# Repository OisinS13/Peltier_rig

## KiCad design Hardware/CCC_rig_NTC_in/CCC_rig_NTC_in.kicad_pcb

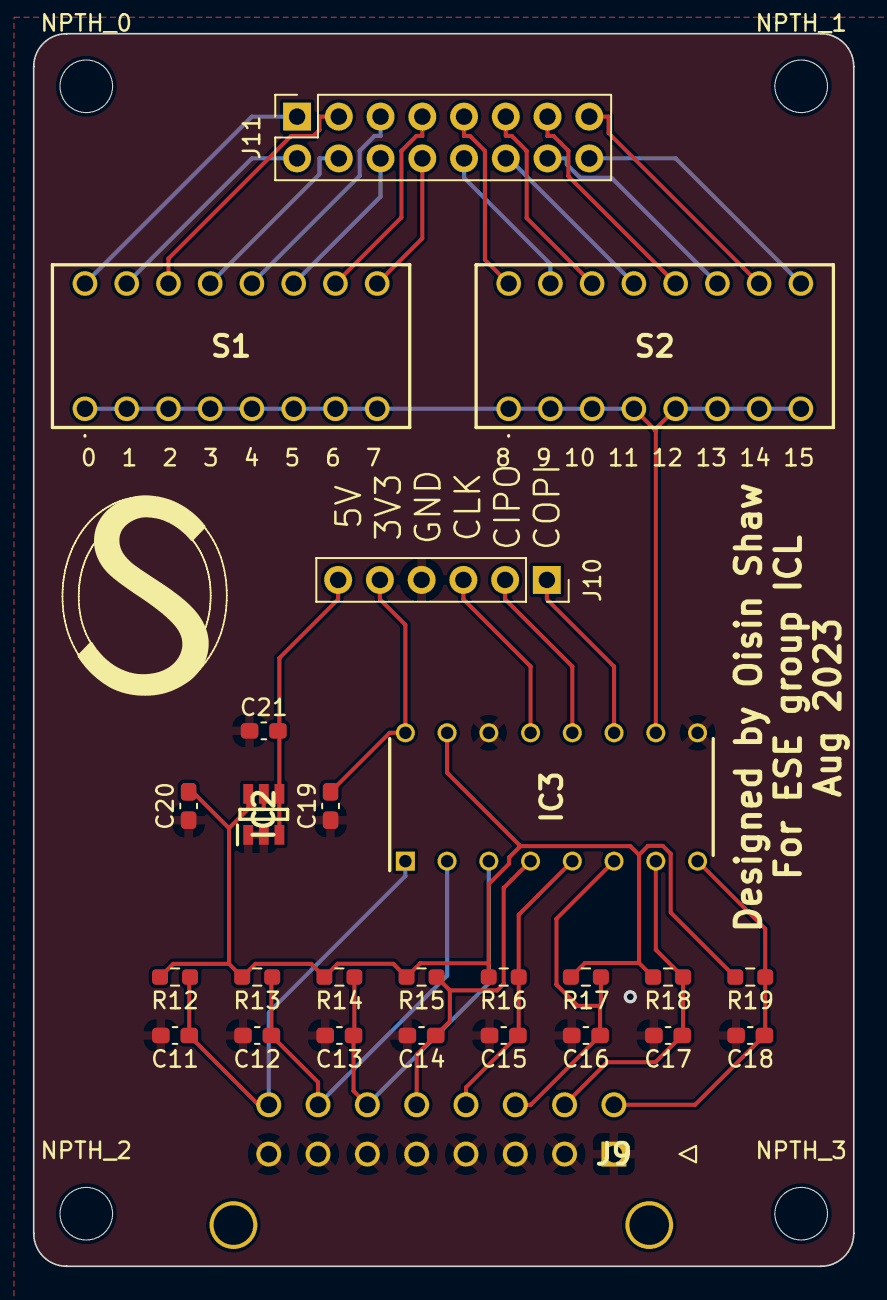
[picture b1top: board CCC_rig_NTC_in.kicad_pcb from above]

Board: 2 copper layers, 49.9 x 75.0 mm, 30 parts (0 on the bottom side), 32 nets.

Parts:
C11, C12, C13, C14, C15, C16, C17, C18, C19, C20: 10 nF; C_0603_1608Metric_Pad1.08x0.95mm_HandSolder
C21: 1 uF; C_0603_1608Metric_Pad1.08x0.95mm_HandSolder
IC2: REF3433IDBVR; SOT95P280X145-6N
IC3: MCP3304-CI_P; DIP781W56P254L1918H533Q16N
J9: NTC_Conn; 43045-16YY_212223
J10: NTC_ADC_Conn; PinSocket_1x06_P2.54mm_Vertical
J11: NTC_ADC_CS_Conn; PinSocket_2x08_P2.54mm_Vertical
NPTH_0, NPTH_1, NPTH_2, NPTH_3: MountingHole_3.2mm_M3_ISO7380
R12, R13, R14, R15, R16, R17, R18, R19: 6.8k; R_0603_1608Metric_Pad0.98x0.95mm_HandSolder
S1, S2: DS01C-254-S-08BE; DS01C254S08BE

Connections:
3V3_ref_NTC_ADC: C20.2, IC2.5 (OUT_S), IC2.6 (OUT_F), IC3.15 (VREF), R12.2, R13.2, R14.2, R15.2, R16.2, R17.2, R18.2, R19.2
+3.3V: C19.2, IC3.16 (VDD), J10.5
+5V: C21.2, IC2.3 (ENABLE), IC2.4 (IN), J10.6
ADC_SPI_CLK: IC3.13 (CLK), J10.3
ADC_SPI_MISO: IC3.12 (DOUT), J10.2
ADC_SPI_MOSI: IC3.11 (DIN), J10.1
GNDD: C11.2, C12.2, C13.2, C14.2, C15.2, C16.2, C17.2, C18.2, C19.1, C20.1, C21.1, IC2.1 (GND_F), IC2.2 (GND_S), IC3.9 (DGND), IC3.14 (AGND), J9.1, J9.2, J9.3, J9.4, J9.5, J9.6, J9.7, J9.8, J10.4
NTC_ADC_CH0: C11.1, IC3.1 (CH0), J9.16, R12.1
NTC_ADC_CH1: C12.1, IC3.2 (CH1), J9.15, R13.1
NTC_ADC_CH2: C13.1, IC3.3 (CH2), J9.14, R14.1
NTC_ADC_CH3: C14.1, IC3.4 (CH3), J9.13, R15.1
NTC_ADC_CH4: C15.1, IC3.5 (CH4), J9.12, R16.1
NTC_ADC_CH5: C16.1, IC3.6 (CH5), J9.11, R17.1
NTC_ADC_CH6: C17.1, IC3.7 (CH6), J9.10, R18.1
NTC_ADC_CH7: C18.1, IC3.8 (CH7), J9.9, R19.1
NTC_ADC_CS: IC3.10 (~CS/SHDN), S1.1 (COM_1), S1.3 (COM_2), S1.5 (COM_3), S1.7 (COM_4), S1.9 (COM_5), S1.11 (COM_6), S1.13 (COM_7), S1.15 (COM_8), S2.1 (COM_1), S2.3 (COM_2), S2.5 (COM_3), S2.7 (COM_4), S2.9 (COM_5), S2.11 (COM_6), S2.13 (COM_7), S2.15 (COM_8)
NTC_ADC_CS_00: J11.1, S1.2 (NO_1)
NTC_ADC_CS_01: J11.2, S1.4 (NO_2)
NTC_ADC_CS_02: J11.3, S1.6 (NO_3)
NTC_ADC_CS_03: J11.4, S1.8 (NO_4)
NTC_ADC_CS_04: J11.5, S1.10 (NO_5)
NTC_ADC_CS_05: J11.6, S1.12 (NO_6)
NTC_ADC_CS_06: J11.7, S1.14 (NO_7)
NTC_ADC_CS_07: J11.8, S1.16 (NO_8)
NTC_ADC_CS_08: J11.9, S2.2 (NO_1)
NTC_ADC_CS_09: J11.10, S2.4 (NO_2)
NTC_ADC_CS_10: J11.11, S2.6 (NO_3)
NTC_ADC_CS_11: J11.12, S2.8 (NO_4)
NTC_ADC_CS_12: J11.13, S2.10 (NO_5)
NTC_ADC_CS_13: J11.14, S2.12 (NO_6)
NTC_ADC_CS_14: J11.15, S2.14 (NO_7)
NTC_ADC_CS_15: J11.16, S2.16 (NO_8)

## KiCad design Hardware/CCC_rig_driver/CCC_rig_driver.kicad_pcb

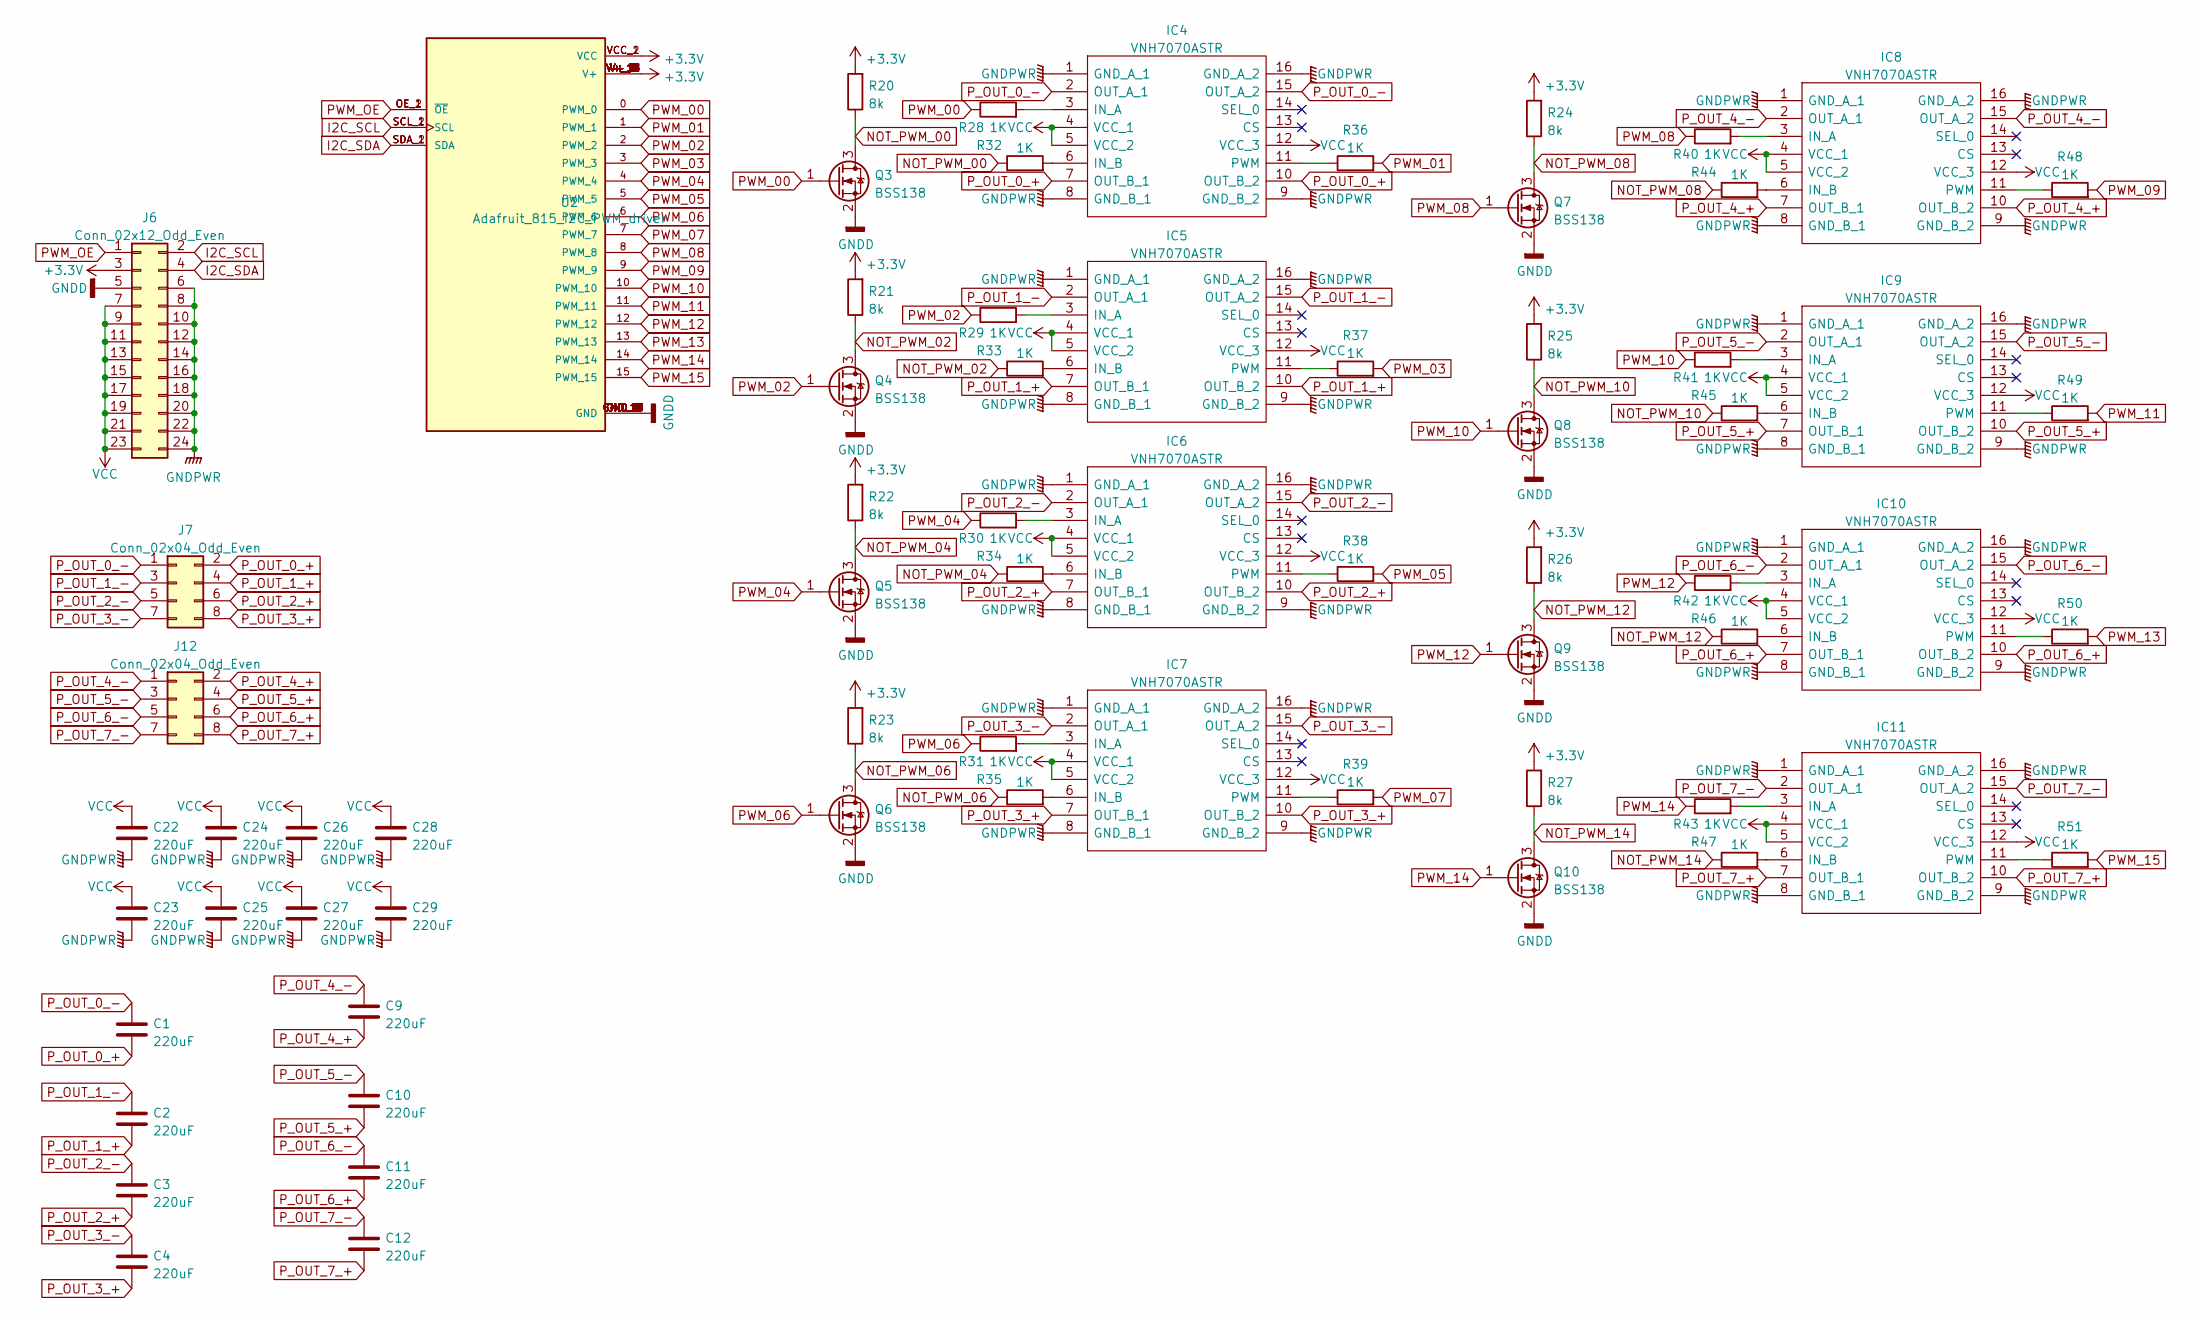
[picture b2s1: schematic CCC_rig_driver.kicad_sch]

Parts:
C1, C2, C3, C4, C9, C10, C11, C12: 220uF; CP_Radial_D5.0mm_P2.50mm
C22, C23, C24, C25, C26, C27, C28, C29: 220uF; CP_Radial_D8.0mm_P3.50mm
IC4, IC5, IC6, IC7, IC8, IC9, IC10, IC11: VNH7070ASTR; SOIC127P600X175-16N-layout; Mouser Part Number 511-VNH7070ASTR
J6: Conn_02x12_Odd_Even; TE-5530843-1-2x12_edge_connector
J7, J12: Conn_02x04_Odd_Even; Anderson_PCB_mount_P1545_2x4
Q3, Q4, Q5, Q6, Q7, Q8, Q9, Q10: BSS138; SOT-23
R20, R21, R22, R23, R24, R25, R26, R27: 8k; R_0603_1608Metric_Pad0.98x0.95mm_HandSolder
R28, R29, R30, R31, R32, R33, R34, R35, R36, R37, R38, R39, R40, R41, R42, R43, R44, R45, R46, R47, R48, R49, R50, R51: 1K; R_0603_1608Metric_Pad0.98x0.95mm_HandSolder
U2: Adafruit_815_I2C_PWM_driver; MODULE_815

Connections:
+3.3V: J6.3, R20.2, R21.2, R22.2, R23.2, R24.2, R25.2, R26.2, R27.2, U2.V+_1 (V+), U2.V+_2 (V+), U2.V+_3 (V+), U2.V+_4 (V+), U2.V+_5 (V+), U2.V+_6 (V+), U2.V+_7 (V+), U2.V+_8 (V+), U2.V+_9 (V+), U2.V+_10 (V+), U2.V+_11 (V+), U2.V+_12 (V+), U2.V+_13 (V+), U2.V+_14 (V+), U2.V+_15 (V+), U2.V+_16 (V+), U2.V+_17 (V+), U2.V+_18 (V+), U2.VCC_1 (VCC), U2.VCC_2 (VCC)
GNDD: J6.5, Q3.2 (S), Q4.2 (S), Q5.2 (S), Q6.2 (S), Q7.2 (S), Q8.2 (S), Q9.2 (S), Q10.2 (S), U2.GND_1 (GND), U2.GND_2 (GND), U2.GND_3 (GND), U2.GND_4 (GND), U2.GND_5 (GND), U2.GND_6 (GND), U2.GND_7 (GND), U2.GND_8 (GND), U2.GND_9 (GND), U2.GND_10 (GND), U2.GND_11 (GND), U2.GND_12 (GND), U2.GND_13 (GND), U2.GND_14 (GND), U2.GND_15 (GND), U2.GND_16 (GND), U2.GND_17 (GND), U2.GND_18 (GND)
GNDPWR: C22.2, C23.2, C24.2, C25.2, C26.2, C27.2, C28.2, C29.2, IC4.1 (GND_A_1), IC4.8 (GND_B_1), IC4.9 (GND_B_2), IC4.16 (GND_A_2), IC5.1 (GND_A_1), IC5.8 (GND_B_1), IC5.9 (GND_B_2), IC5.16 (GND_A_2), IC6.1 (GND_A_1), IC6.8 (GND_B_1), IC6.9 (GND_B_2), IC6.16 (GND_A_2), IC7.1 (GND_A_1), IC7.8 (GND_B_1), IC7.9 (GND_B_2), IC7.16 (GND_A_2), IC8.1 (GND_A_1), IC8.8 (GND_B_1), IC8.9 (GND_B_2), IC8.16 (GND_A_2), IC9.1 (GND_A_1), IC9.8 (GND_B_1), IC9.9 (GND_B_2), IC9.16 (GND_A_2), IC10.1 (GND_A_1), IC10.8 (GND_B_1), IC10.9 (GND_B_2), IC10.16 (GND_A_2), IC11.1 (GND_A_1), IC11.8 (GND_B_1), IC11.9 (GND_B_2), IC11.16 (GND_A_2), J6.6, J6.8, J6.10, J6.12, J6.14, J6.16, J6.18, J6.20, J6.22, J6.24
I2C_SCL: J6.2, U2.SCL_1 (SCL), U2.SCL_2 (SCL)
I2C_SDA: J6.4, U2.SDA_1 (SDA), U2.SDA_2 (SDA)
NOT_PWM_00: Q3.3 (D), R20.1, R32.1
NOT_PWM_02: Q4.3 (D), R21.1, R33.1
NOT_PWM_04: Q5.3 (D), R22.1, R34.1
NOT_PWM_06: Q6.3 (D), R23.1, R35.1
NOT_PWM_08: Q7.3 (D), R24.1, R44.1
NOT_PWM_10: Q8.3 (D), R25.1, R45.1
NOT_PWM_12: Q9.3 (D), R26.1, R46.1
NOT_PWM_14: Q10.3 (D), R27.1, R47.1
unnamed: IC4.3 (IN_A), R28.2
unnamed: IC4.6 (IN_B), R32.2
unnamed: IC4.11 (PWM), R36.1
unnamed: IC5.3 (IN_A), R29.2
unnamed: IC5.6 (IN_B), R33.2
unnamed: IC5.11 (PWM), R37.1
unnamed: IC6.3 (IN_A), R30.2
unnamed: IC6.6 (IN_B), R34.2
unnamed: IC6.11 (PWM), R38.1
unnamed: IC7.3 (IN_A), R31.2
unnamed: IC7.6 (IN_B), R35.2
unnamed: IC7.11 (PWM), R39.1
unnamed: IC8.3 (IN_A), R40.2
unnamed: IC8.6 (IN_B), R44.2
unnamed: IC8.11 (PWM), R48.1
unnamed: IC9.3 (IN_A), R41.2
unnamed: IC9.6 (IN_B), R45.2
unnamed: IC9.11 (PWM), R49.1
unnamed: IC10.3 (IN_A), R42.2
unnamed: IC10.6 (IN_B), R46.2
unnamed: IC10.11 (PWM), R50.1
unnamed: IC11.3 (IN_A), R43.2
unnamed: IC11.6 (IN_B), R47.2
unnamed: IC11.11 (PWM), R51.1
PWM_00: Q3.1 (G), R28.1, U2.0 (PWM_0)
PWM_01: R36.2, U2.1 (PWM_1)
PWM_02: Q4.1 (G), R29.1, U2.2 (PWM_2)
PWM_03: R37.2, U2.3 (PWM_3)
PWM_04: Q5.1 (G), R30.1, U2.4 (PWM_4)
PWM_05: R38.2, U2.5 (PWM_5)
PWM_06: Q6.1 (G), R31.1, U2.6 (PWM_6)
PWM_07: R39.2, U2.7 (PWM_7)
PWM_08: Q7.1 (G), R40.1, U2.8 (PWM_8)
PWM_09: R48.2, U2.9 (PWM_9)
PWM_10: Q8.1 (G), R41.1, U2.10 (PWM_10)
PWM_11: R49.2, U2.11 (PWM_11)
PWM_12: Q9.1 (G), R42.1, U2.12 (PWM_12)
PWM_13: R50.2, U2.13 (PWM_13)
PWM_14: Q10.1 (G), R43.1, U2.14 (PWM_14)
PWM_15: R51.2, U2.15 (PWM_15)
PWM_OE: J6.1, U2.OE_1 (~OE), U2.OE_2 (~OE)
P_OUT_0_+: C1.2, IC4.7 (OUT_B_1), IC4.10 (OUT_B_2), J7.2
P_OUT_0_-: C1.1, IC4.2 (OUT_A_1), IC4.15 (OUT_A_2), J7.1
P_OUT_1_+: C2.2, IC5.7 (OUT_B_1), IC5.10 (OUT_B_2), J7.4
P_OUT_1_-: C2.1, IC5.2 (OUT_A_1), IC5.15 (OUT_A_2), J7.3
P_OUT_2_+: C3.2, IC6.7 (OUT_B_1), IC6.10 (OUT_B_2), J7.6
P_OUT_2_-: C3.1, IC6.2 (OUT_A_1), IC6.15 (OUT_A_2), J7.5
P_OUT_3_+: C4.2, IC7.7 (OUT_B_1), IC7.10 (OUT_B_2), J7.8
P_OUT_3_-: C4.1, IC7.2 (OUT_A_1), IC7.15 (OUT_A_2), J7.7
P_OUT_4_+: C9.2, IC8.7 (OUT_B_1), IC8.10 (OUT_B_2), J12.2
P_OUT_4_-: C9.1, IC8.2 (OUT_A_1), IC8.15 (OUT_A_2), J12.1
P_OUT_5_+: C10.2, IC9.7 (OUT_B_1), IC9.10 (OUT_B_2), J12.4
P_OUT_5_-: C10.1, IC9.2 (OUT_A_1), IC9.15 (OUT_A_2), J12.3
P_OUT_6_+: C11.2, IC10.7 (OUT_B_1), IC10.10 (OUT_B_2), J12.6
P_OUT_6_-: C11.1, IC10.2 (OUT_A_1), IC10.15 (OUT_A_2), J12.5
P_OUT_7_+: C12.2, IC11.7 (OUT_B_1), IC11.10 (OUT_B_2), J12.8
P_OUT_7_-: C12.1, IC11.2 (OUT_A_1), IC11.15 (OUT_A_2), J12.7
VCC: C22.1, C23.1, C24.1, C25.1, C26.1, C27.1, C28.1, C29.1, IC4.4 (VCC_1), IC4.5 (VCC_2), IC4.12 (VCC_3), IC5.4 (VCC_1), IC5.5 (VCC_2), IC5.12 (VCC_3), IC6.4 (VCC_1), IC6.5 (VCC_2), IC6.12 (VCC_3), IC7.4 (VCC_1), IC7.5 (VCC_2), IC7.12 (VCC_3), IC8.4 (VCC_1), IC8.5 (VCC_2), IC8.12 (VCC_3), IC9.4 (VCC_1), IC9.5 (VCC_2), IC9.12 (VCC_3), IC10.4 (VCC_1), IC10.5 (VCC_2), IC10.12 (VCC_3), IC11.4 (VCC_1), IC11.5 (VCC_2), IC11.12 (VCC_3), J6.7, J6.9, J6.11, J6.13, J6.15, J6.17, J6.19, J6.21, J6.23

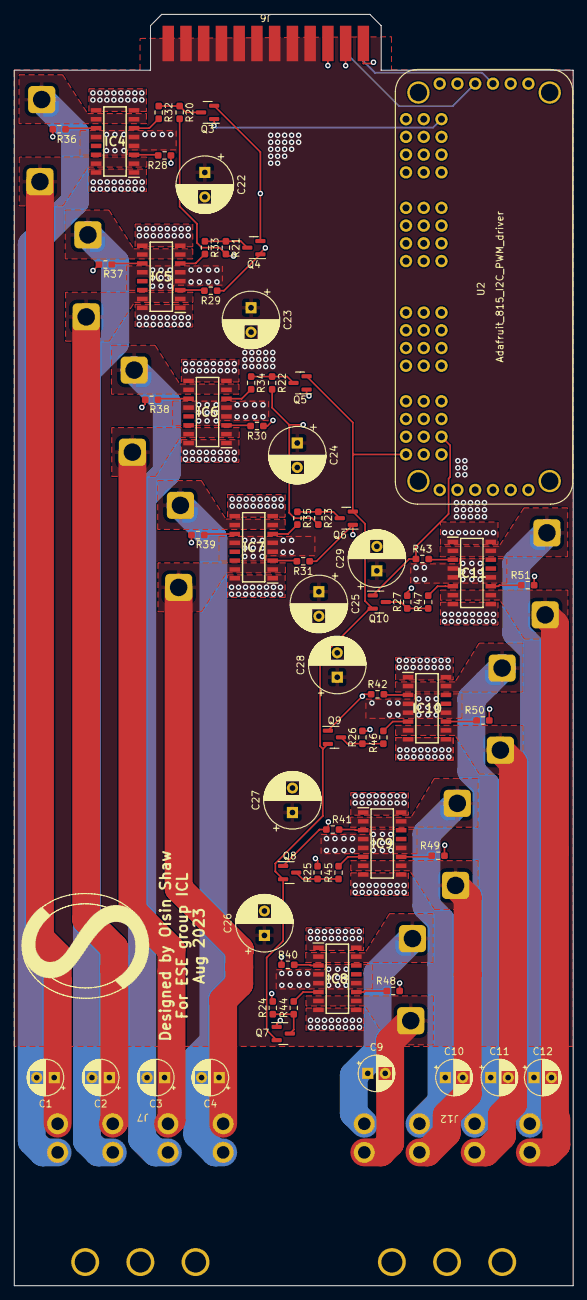
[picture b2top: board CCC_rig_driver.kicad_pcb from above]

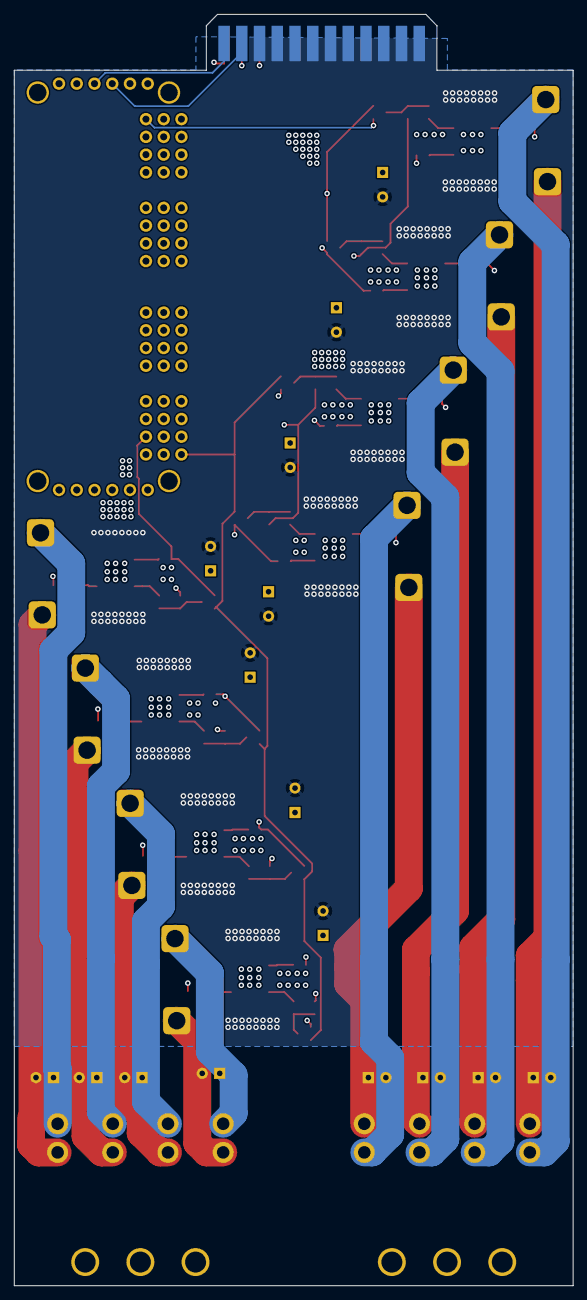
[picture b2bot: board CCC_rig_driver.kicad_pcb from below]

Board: 4 copper layers, 80.0 x 182.0 mm, 68 parts (2 on the bottom side), 71 nets.

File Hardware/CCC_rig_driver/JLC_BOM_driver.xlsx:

Comment | Designator | Footprint | JLCPCB Part #（optional）
VNH7070ASTR | IC4 IC5 IC6 IC7 IC8 IC9 IC10 IC11 | SamacSys_Parts:SOIC127P600X175-16N-layout | C2150622
BSS138 | Q3 Q4 Q5 Q6 Q7 Q8 Q9 Q10 | Package_TO_SOT_SMD:SOT-23 | C112239
8.06k | R20 R21 R22 R23 R24 R25 R26 R27 | Resistor_SMD:R_0603_1608Metric_Pad0.98x0.95mm_HandSolder | C861587
1k | R28 R29 R30 R31 R32 R33 R34 R35 R36 R37 R38 R39 R40 R41 R42 R43 R44 R45 R46 R47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 | Resistor_SMD:R_0603_1608Metric_Pad0.98x0.95mm_HandSolder | C22548

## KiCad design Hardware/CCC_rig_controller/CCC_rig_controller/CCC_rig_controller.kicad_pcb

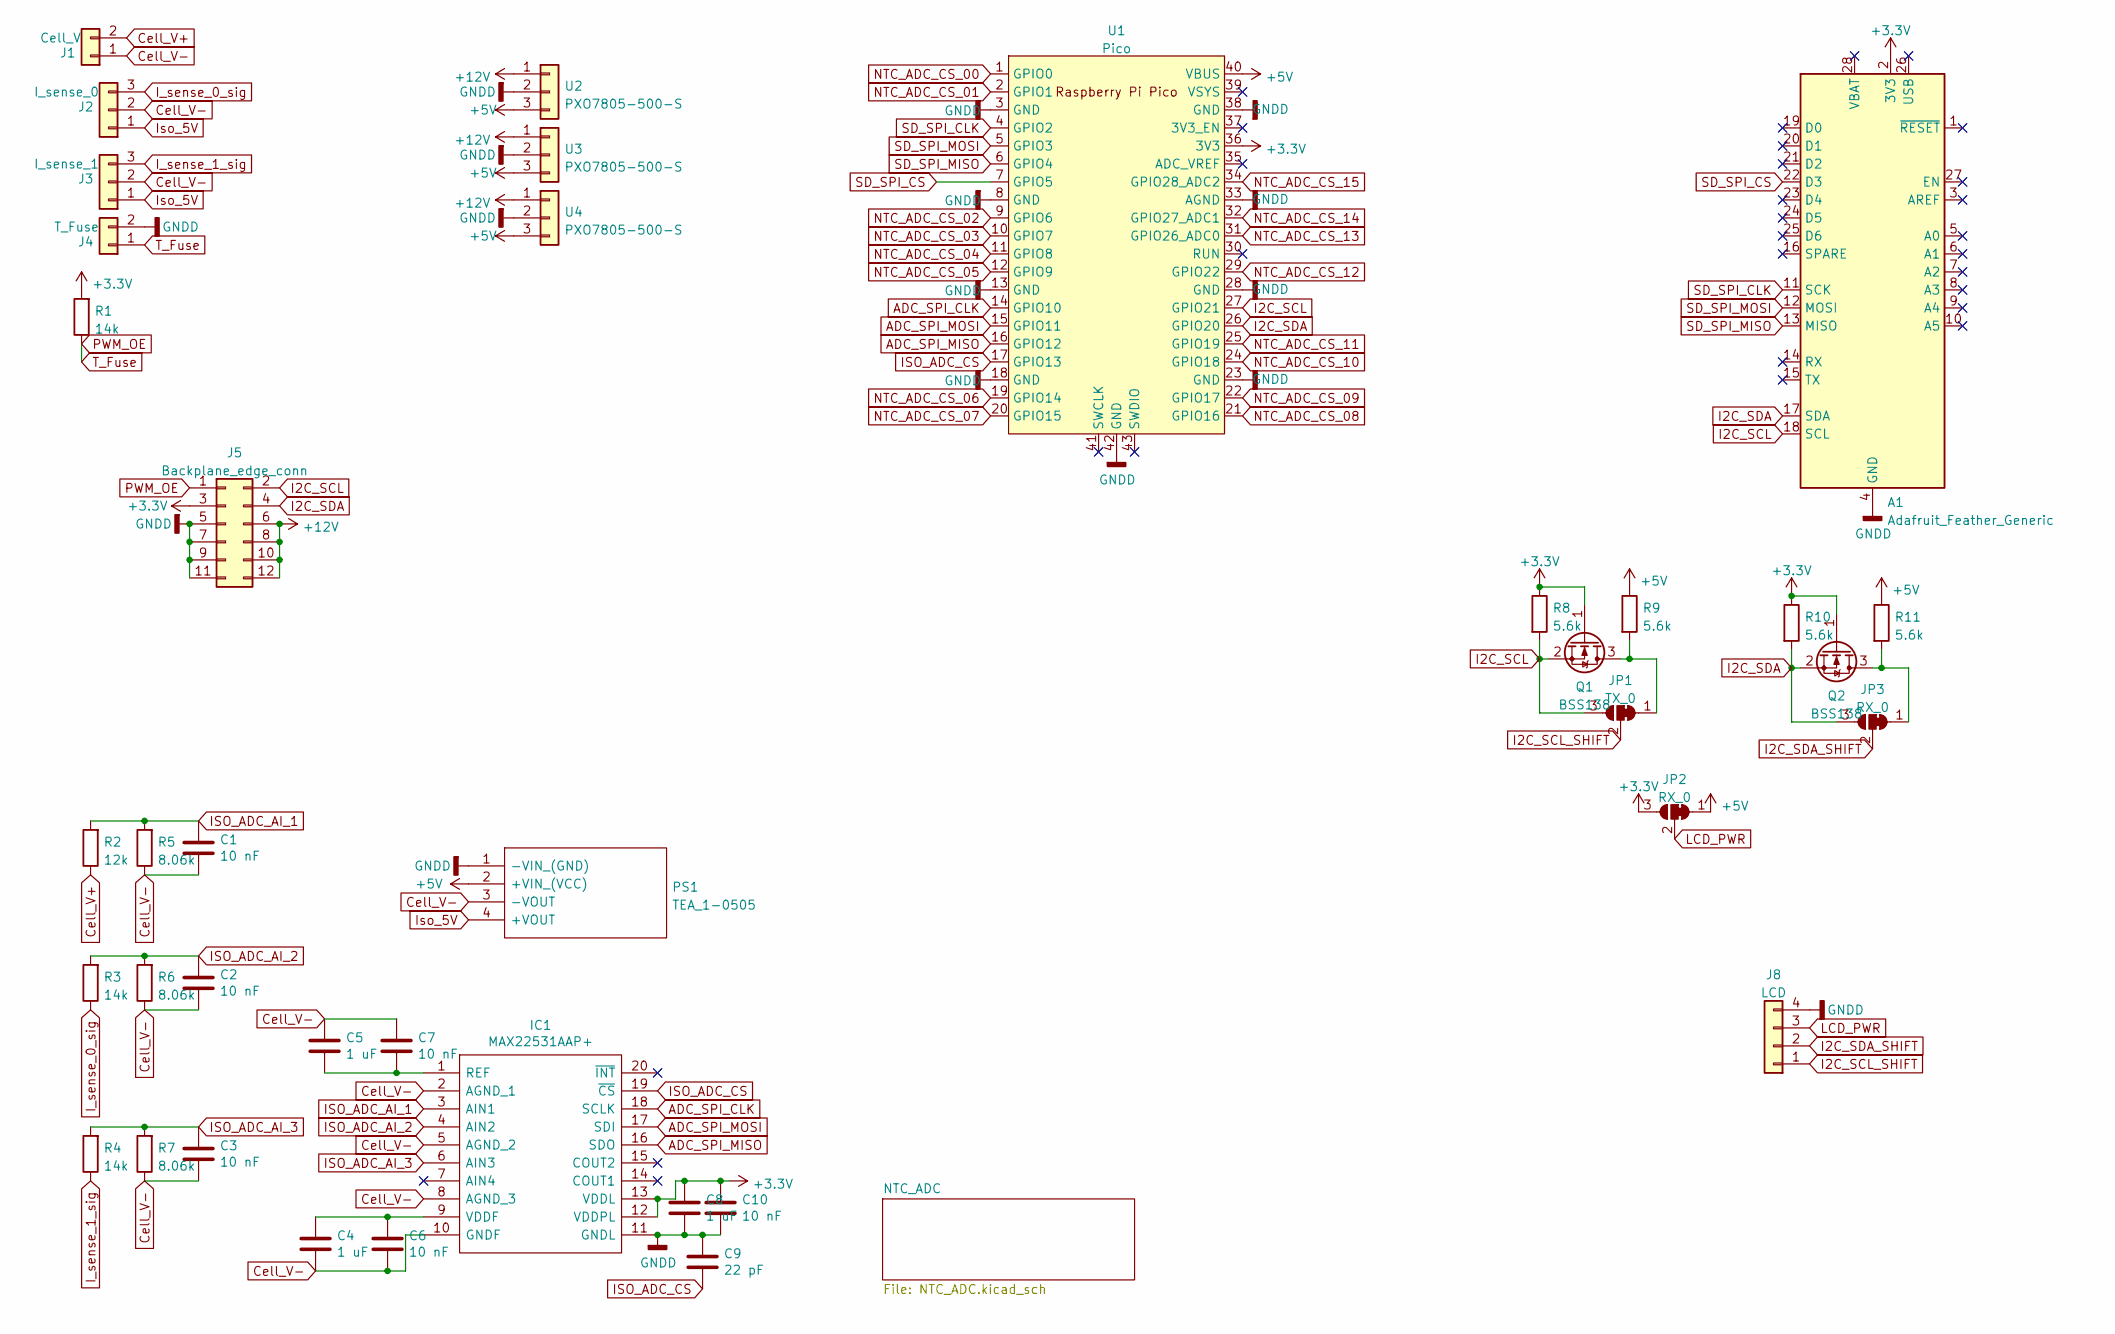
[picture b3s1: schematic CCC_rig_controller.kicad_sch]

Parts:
A1: Adafruit_Feather_Generic; Adafruit_Feather
C1, C2, C3, C6, C7, C10: 10 nF; C_0603_1608Metric_Pad1.08x0.95mm_HandSolder
C4, C5, C8: 1 uF; C_0603_1608Metric_Pad1.08x0.95mm_HandSolder
C9: 22 pF; C_0603_1608Metric_Pad1.08x0.95mm_HandSolder
IC1: MAX22531AAP+; SOP65P778X199-20N; Mouser Part Number 700-MAX22531AAP+
J1: Cell_V; 1963531
J2: I_sense_0; 1963544
J3: I_sense_1; 1963544
J4: T_Fuse; 1963531
J5: Backplane_edge_conn; TE-7-5530843-5-2x6_edge_connector
J8: LCD; 1963557
JP1: TX_0; SolderJumper-3_P1.3mm_Bridged2Bar12_RoundedPad1.0x1.5mm
JP2, JP3: RX_0; SolderJumper-3_P1.3mm_Bridged2Bar12_RoundedPad1.0x1.5mm
PS1: TEA_1-0505; TEA10505; Mouser Part Number 495-TEA1-0505
Q1, Q2: BSS138; SOT-23
R1, R3, R4: 14k; R_0603_1608Metric_Pad0.98x0.95mm_HandSolder
R2: 12k; R_0603_1608Metric_Pad0.98x0.95mm_HandSolder
R5, R6, R7: 8.06k; R_0603_1608Metric_Pad0.98x0.95mm_HandSolder
R8, R9, R10, R11: 5.6k; R_0603_1608Metric_Pad0.98x0.95mm_HandSolder
U1: Pico; RPi_Pico_SMD_TH
U2, U3, U4: PXO7805-500-S

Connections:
+3.3V: A1.2 (3V3), C8.1, C10.1, IC1.12 (VDDPL), IC1.13 (VDDL), J5.3, JP2.3 (B), Q1.1 (G), Q2.1 (G), R1.2, R8.1, R10.1, U1.36 (3V3); also elsewhere on the board
+5V: JP2.1 (A), PS1.2 (+VIN_(VCC)), R9.1, R11.1, U1.40 (VBUS), U2.3, U3.3, U4.3; also elsewhere on the board
+12V: J5.6, J5.8, J5.10, J5.12, U2.1, U3.1, U4.1
ADC_SPI_CLK: IC1.18 (SCLK), U1.14 (GPIO10)
ADC_SPI_MISO: IC1.16 (SDO), U1.16 (GPIO12)
ADC_SPI_MOSI: IC1.17 (SDI), U1.15 (GPIO11)
Cell_V+: J1.2, R2.1
Cell_V-: C1.2, C2.2, C3.2, C4.2, C5.1, C6.2, C7.1, IC1.2 (AGND_1), IC1.5 (AGND_2), IC1.8 (AGND_3), IC1.10 (GNDF), J1.1, J2.2, J3.2, PS1.3 (-VOUT), R5.1, R6.1, R7.1
GNDD: A1.4 (GND), C8.2, C9.1, C10.2, IC1.11 (GNDL), J4.2, J5.5, J5.7, J5.9, J5.11, J8.4, PS1.1 (-VIN_(GND)), U1.3 (GND), U1.8 (GND), U1.13 (GND), U1.18 (GND), U1.23 (GND), U1.28 (GND), U1.33 (AGND), U1.38 (GND), U1.42 (GND), U2.2, U3.2, U4.2; also elsewhere on the board
I2C_SCL: A1.18 (SCL), J5.2, JP1.3 (B), Q1.2 (S), R8.2, U1.27 (GPIO21)
I2C_SCL_SHIFT: J8.1, JP1.2 (C)
I2C_SDA: A1.17 (SDA), J5.4, JP3.3 (B), Q2.2 (S), R10.2, U1.26 (GPIO20)
I2C_SDA_SHIFT: J8.2, JP3.2 (C)
ISO_ADC_AI_1: C1.1, IC1.3 (AIN1), R2.2, R5.2
ISO_ADC_AI_2: C2.1, IC1.4 (AIN2), R3.2, R6.2
ISO_ADC_AI_3: C3.1, IC1.6 (AIN3), R4.2, R7.2
ISO_ADC_CS: C9.2, IC1.19 (~CS), U1.17 (GPIO13)
I_sense_0_sig: J2.3, R3.1
I_sense_1_sig: J3.3, R4.1
Iso_5V: J2.1, J3.1, PS1.4 (+VOUT)
LCD_PWR: J8.3, JP2.2 (C)
NTC_ADC_CS_00: U1.1 (GPIO0); also elsewhere on the board
NTC_ADC_CS_01: U1.2 (GPIO1); also elsewhere on the board
NTC_ADC_CS_02: U1.9 (GPIO6); also elsewhere on the board
NTC_ADC_CS_03: U1.10 (GPIO7); also elsewhere on the board
NTC_ADC_CS_04: U1.11 (GPIO8); also elsewhere on the board
NTC_ADC_CS_05: U1.12 (GPIO9); also elsewhere on the board
NTC_ADC_CS_06: U1.19 (GPIO14); also elsewhere on the board
NTC_ADC_CS_07: U1.20 (GPIO15); also elsewhere on the board
NTC_ADC_CS_08: U1.21 (GPIO16); also elsewhere on the board
NTC_ADC_CS_09: U1.22 (GPIO17); also elsewhere on the board
NTC_ADC_CS_10: U1.24 (GPIO18); also elsewhere on the board
NTC_ADC_CS_11: U1.25 (GPIO19); also elsewhere on the board
NTC_ADC_CS_12: U1.29 (GPIO22); also elsewhere on the board
NTC_ADC_CS_13: U1.31 (GPIO26_ADC0); also elsewhere on the board
NTC_ADC_CS_14: U1.32 (GPIO27_ADC1); also elsewhere on the board
NTC_ADC_CS_15: U1.34 (GPIO28_ADC2); also elsewhere on the board
unnamed: C4.1, C6.1, IC1.9 (VDDF)
unnamed: C5.2, C7.2, IC1.1 (REF)
unnamed: JP1.1 (A), Q1.3 (D), R9.2
unnamed: JP3.1 (A), Q2.3 (D), R11.2
PWM_OE: J4.1, J5.1, R1.1
SD_SPI_CLK: A1.11 (SCK), U1.4 (GPIO2); also elsewhere on the board
SD_SPI_CS: A1.22 (D3), U1.7 (GPIO5)
SD_SPI_MISO: A1.13 (MISO), U1.6 (GPIO4); also elsewhere on the board
SD_SPI_MOSI: A1.12 (MOSI), U1.5 (GPIO3); also elsewhere on the board

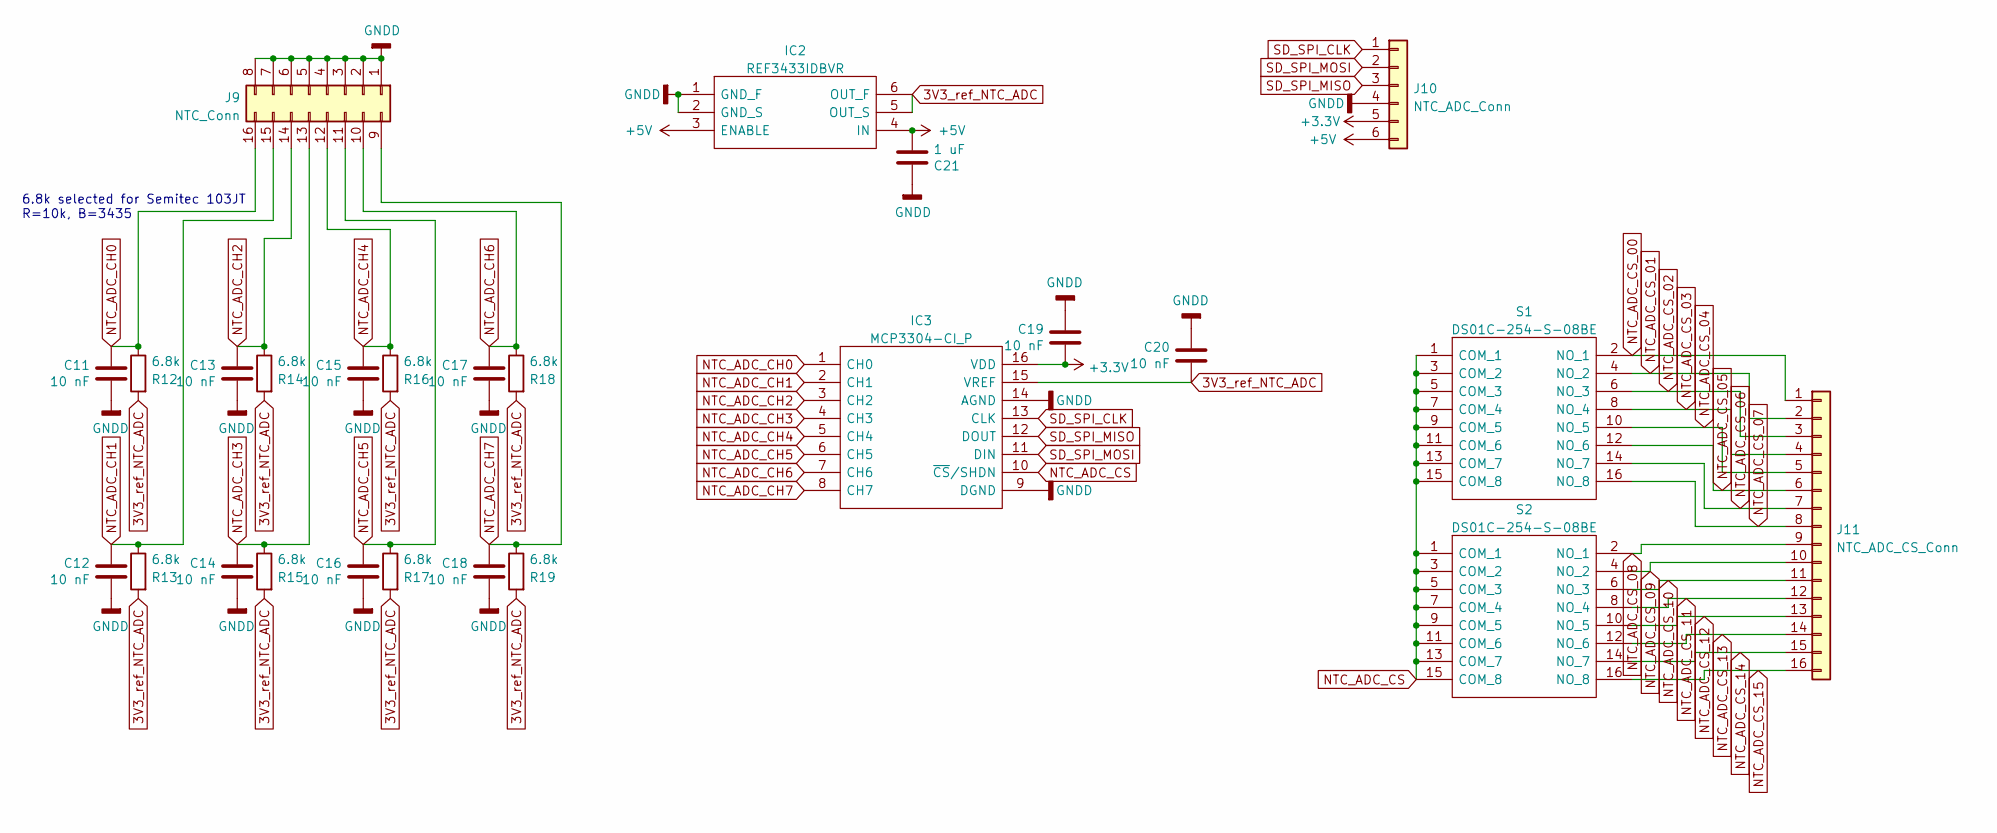
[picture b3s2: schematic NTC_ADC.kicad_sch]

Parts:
C11, C12, C13, C14, C15, C16, C17, C18, C19, C20: 10 nF; C_0603_1608Metric_Pad1.08x0.95mm_HandSolder
C21: 1 uF; C_0603_1608Metric_Pad1.08x0.95mm_HandSolder
IC2: REF3433IDBVR; SOT95P280X145-6N; Mouser Part Number 595-REF3433IDBVR
IC3: MCP3304-CI_P; DIP781W56P254L1918H533Q16N; Mouser Part Number 579-MCP3304-CI/P
J9: NTC_Conn; 43045-16YY_212223
J10: NTC_ADC_Conn; PinSocket_1x06_P2.54mm_Vertical
J11: NTC_ADC_CS_Conn; PinSocket_2x08_P2.54mm_Vertical
R12, R13, R14, R15, R16, R17, R18, R19: 6.8k; R_0603_1608Metric_Pad0.98x0.95mm_HandSolder
S1, S2: DS01C-254-S-08BE; DS01C254S08BE; Mouser Part Number 490-DS01C-254-S-08BE

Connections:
3V3_ref_NTC_ADC: C20.2, IC2.5 (OUT_S), IC2.6 (OUT_F), IC3.15 (VREF), R12.2, R13.2, R14.2, R15.2, R16.2, R17.2, R18.2, R19.2
+3.3V: C19.2, IC3.16 (VDD), J10.5; also elsewhere on the board
+5V: C21.2, IC2.3 (ENABLE), IC2.4 (IN), J10.6; also elsewhere on the board
GNDD: C11.2, C12.2, C13.2, C14.2, C15.2, C16.2, C17.2, C18.2, C19.1, C20.1, C21.1, IC2.1 (GND_F), IC2.2 (GND_S), IC3.9 (DGND), IC3.14 (AGND), J9.1, J9.2, J9.3, J9.4, J9.5, J9.6, J9.7, J9.8, J10.4; also elsewhere on the board
NTC_ADC_CH0: C11.1, IC3.1 (CH0), J9.16, R12.1
NTC_ADC_CH1: C12.1, IC3.2 (CH1), J9.15, R13.1
NTC_ADC_CH2: C13.1, IC3.3 (CH2), J9.14, R14.1
NTC_ADC_CH3: C14.1, IC3.4 (CH3), J9.13, R15.1
NTC_ADC_CH4: C15.1, IC3.5 (CH4), J9.12, R16.1
NTC_ADC_CH5: C16.1, IC3.6 (CH5), J9.11, R17.1
NTC_ADC_CH6: C17.1, IC3.7 (CH6), J9.10, R18.1
NTC_ADC_CH7: C18.1, IC3.8 (CH7), J9.9, R19.1
NTC_ADC_CS: IC3.10 (~CS/SHDN), S1.1 (COM_1), S1.3 (COM_2), S1.5 (COM_3), S1.7 (COM_4), S1.9 (COM_5), S1.11 (COM_6), S1.13 (COM_7), S1.15 (COM_8), S2.1 (COM_1), S2.3 (COM_2), S2.5 (COM_3), S2.7 (COM_4), S2.9 (COM_5), S2.11 (COM_6), S2.13 (COM_7), S2.15 (COM_8)
NTC_ADC_CS_00: J11.1, S1.2 (NO_1); also elsewhere on the board
NTC_ADC_CS_01: J11.2, S1.4 (NO_2); also elsewhere on the board
NTC_ADC_CS_02: J11.3, S1.6 (NO_3); also elsewhere on the board
NTC_ADC_CS_03: J11.4, S1.8 (NO_4); also elsewhere on the board
NTC_ADC_CS_04: J11.5, S1.10 (NO_5); also elsewhere on the board
NTC_ADC_CS_05: J11.6, S1.12 (NO_6); also elsewhere on the board
NTC_ADC_CS_06: J11.7, S1.14 (NO_7); also elsewhere on the board
NTC_ADC_CS_07: J11.8, S1.16 (NO_8); also elsewhere on the board
NTC_ADC_CS_08: J11.9, S2.2 (NO_1); also elsewhere on the board
NTC_ADC_CS_09: J11.10, S2.4 (NO_2); also elsewhere on the board
NTC_ADC_CS_10: J11.11, S2.6 (NO_3); also elsewhere on the board
NTC_ADC_CS_11: J11.12, S2.8 (NO_4); also elsewhere on the board
NTC_ADC_CS_12: J11.13, S2.10 (NO_5); also elsewhere on the board
NTC_ADC_CS_13: J11.14, S2.12 (NO_6); also elsewhere on the board
NTC_ADC_CS_14: J11.15, S2.14 (NO_7); also elsewhere on the board
NTC_ADC_CS_15: J11.16, S2.16 (NO_8); also elsewhere on the board
SD_SPI_CLK: IC3.13 (CLK), J10.1; also elsewhere on the board
SD_SPI_MISO: IC3.12 (DOUT), J10.3; also elsewhere on the board
SD_SPI_MOSI: IC3.11 (DIN), J10.2; also elsewhere on the board

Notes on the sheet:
6.8k selected for Semitec 103JT R=10k, B=3435

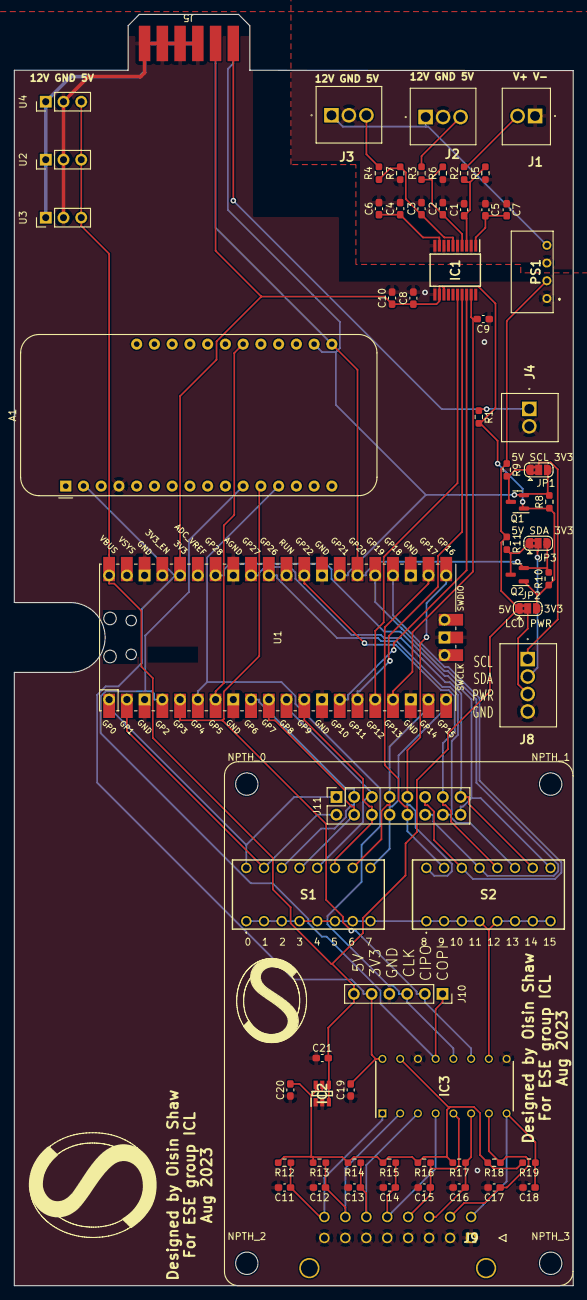
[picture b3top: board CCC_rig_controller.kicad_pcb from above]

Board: 2 copper layers, 80.0 x 182.0 mm, 69 parts (0 on the bottom side), 56 nets.

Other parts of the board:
NPTH_0, NPTH_1, NPTH_2, NPTH_3: MountingHole_3.2mm_M3_ISO7380
